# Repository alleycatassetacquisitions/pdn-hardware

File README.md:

# pdn-hardware
The PCB's for Alleycat's Portable Data Node

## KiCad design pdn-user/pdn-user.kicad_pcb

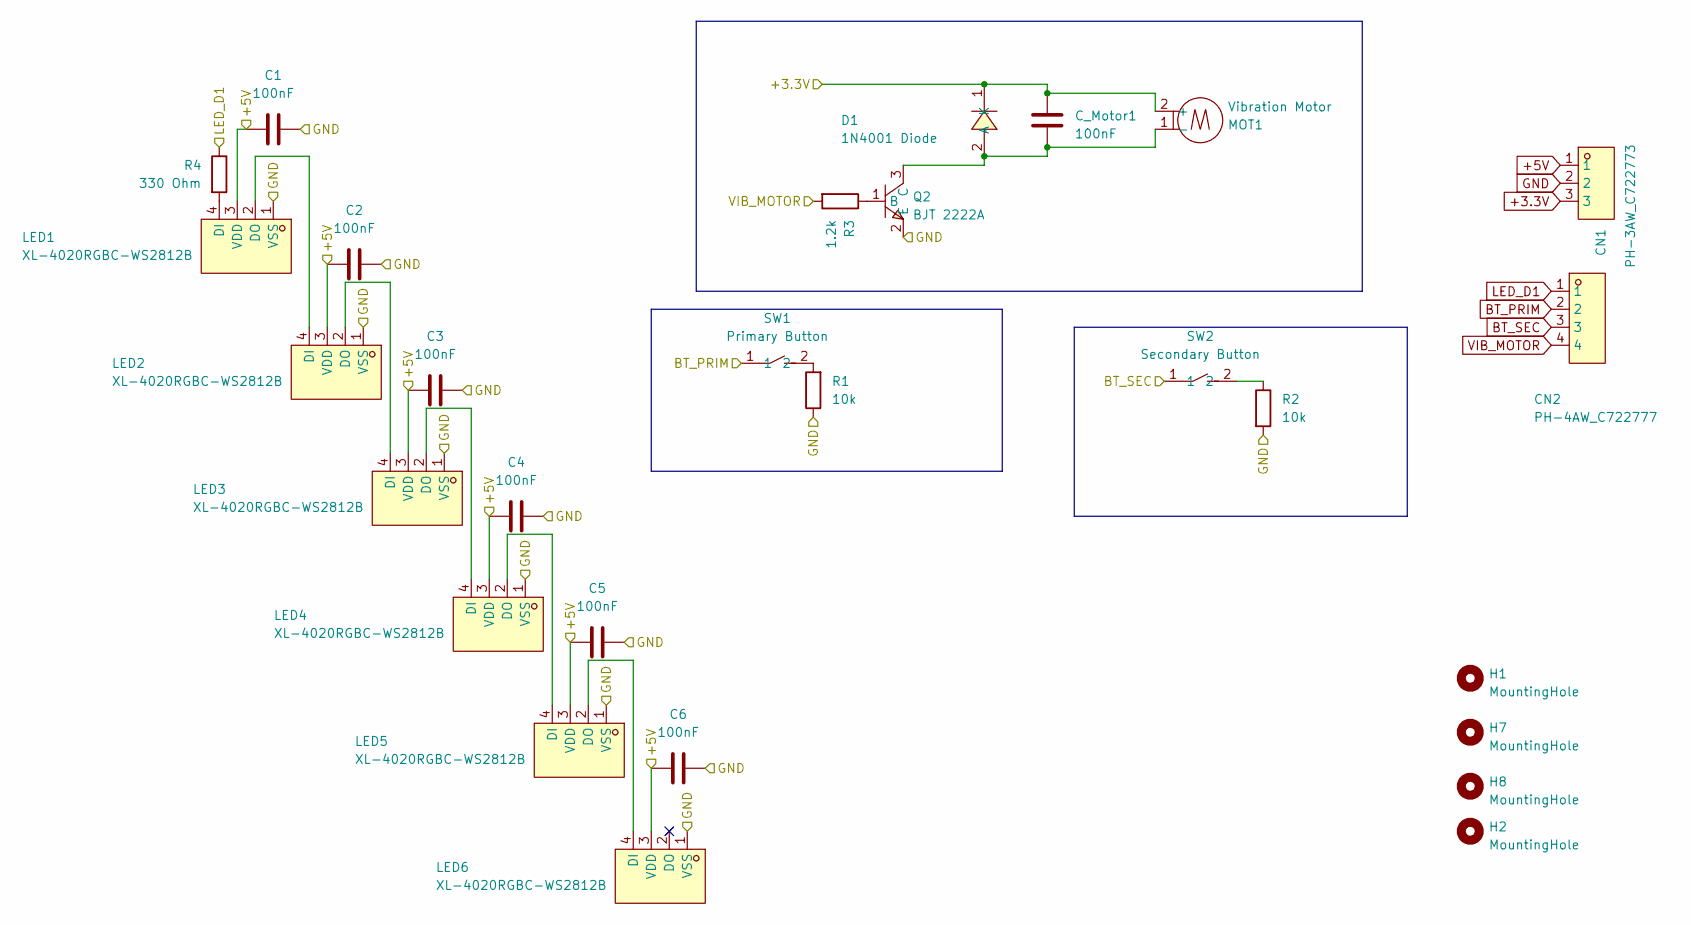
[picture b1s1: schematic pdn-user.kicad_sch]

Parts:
C1, C2, C3, C4, C5, C6: 100nF; C0402; LCSC Part C387958
CN1: PH-3AW_C722773; CONN-TH_PH-3AW; LCSC Part C722773
CN2: PH-4AW_C722777; CONN-TH_PH-4AW_C722777; LCSC Part C722777
C_Motor1: 100nF; C0402; LCSC Part C387958
D1: 1N4001 Diode; SMA_L4.2-W2.6-LS5.0-RD; LCSC Part C2909965
H1, H2, H7, H8: MountingHole; MountingHole_2.2mm_M2_Pad_TopBottom
LED1, LED2, LED3, LED4, LED5, LED6: XL-4020RGBC-WS2812B; LED-SMD_4P-L4.0-W1.7_XL-4020RGBC-WS2812B; LCSC Part C3647024
MOT1: Vibration Motor; VIBRATING-MOTOR-SMD_WELDING; LCSC Part C2759984
Q2: BJT 2222A; SOT-23-3_L2.9-W1.3-P1.90-LS2.4-BR; LCSC Part C916372
R1, R2: 10k; R_0603_1608Metric; LCSC Part C103199
R3: 1.2k; R_0402_1005Metric; LCSC Part C3017481
R4: 330 Ohm; R_0603_1608Metric; LCSC Part C23138
SW1: Primary Button; KEY-SMD_L6.0-W3.5-LS8.0; LCSC Part C2888463
SW2: Secondary Button; KEY-SMD_L6.0-W3.5-LS8.0; LCSC Part C2888463

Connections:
+3.3V: CN1.3, C_Motor1.2, D1.1 (K), MOT1.2 (+)
+5V: C1.1, C2.1, C3.1, C4.1, C5.1, C6.1, CN1.1, LED1.3 (VDD), LED2.3 (VDD), LED3.3 (VDD), LED4.3 (VDD), LED5.3 (VDD), LED6.3 (VDD)
BT_PRIM: CN2.2, SW1.1
BT_SEC: CN2.3, SW2.1
GND: C1.2, C2.2, C3.2, C4.2, C5.2, C6.2, CN1.2, LED1.1 (VSS), LED2.1 (VSS), LED3.1 (VSS), LED4.1 (VSS), LED5.1 (VSS), LED6.1 (VSS), Q2.2 (E), R1.1, R2.2
LED_D1: CN2.1, R4.1
unnamed: C_Motor1.1, D1.2 (A), MOT1.1 (-), Q2.3 (C)
unnamed: LED1.4 (DI), R4.2
unnamed: LED1.2 (DO), LED2.4 (DI)
unnamed: LED2.2 (DO), LED3.4 (DI)
unnamed: LED3.2 (DO), LED4.4 (DI)
unnamed: LED4.2 (DO), LED5.4 (DI)
unnamed: LED5.2 (DO), LED6.4 (DI)
unnamed: Q2.1 (B), R3.1
unnamed: R1.2, SW1.2
unnamed: R2.1, SW2.2
VIB_MOTOR: CN2.4, R3.2

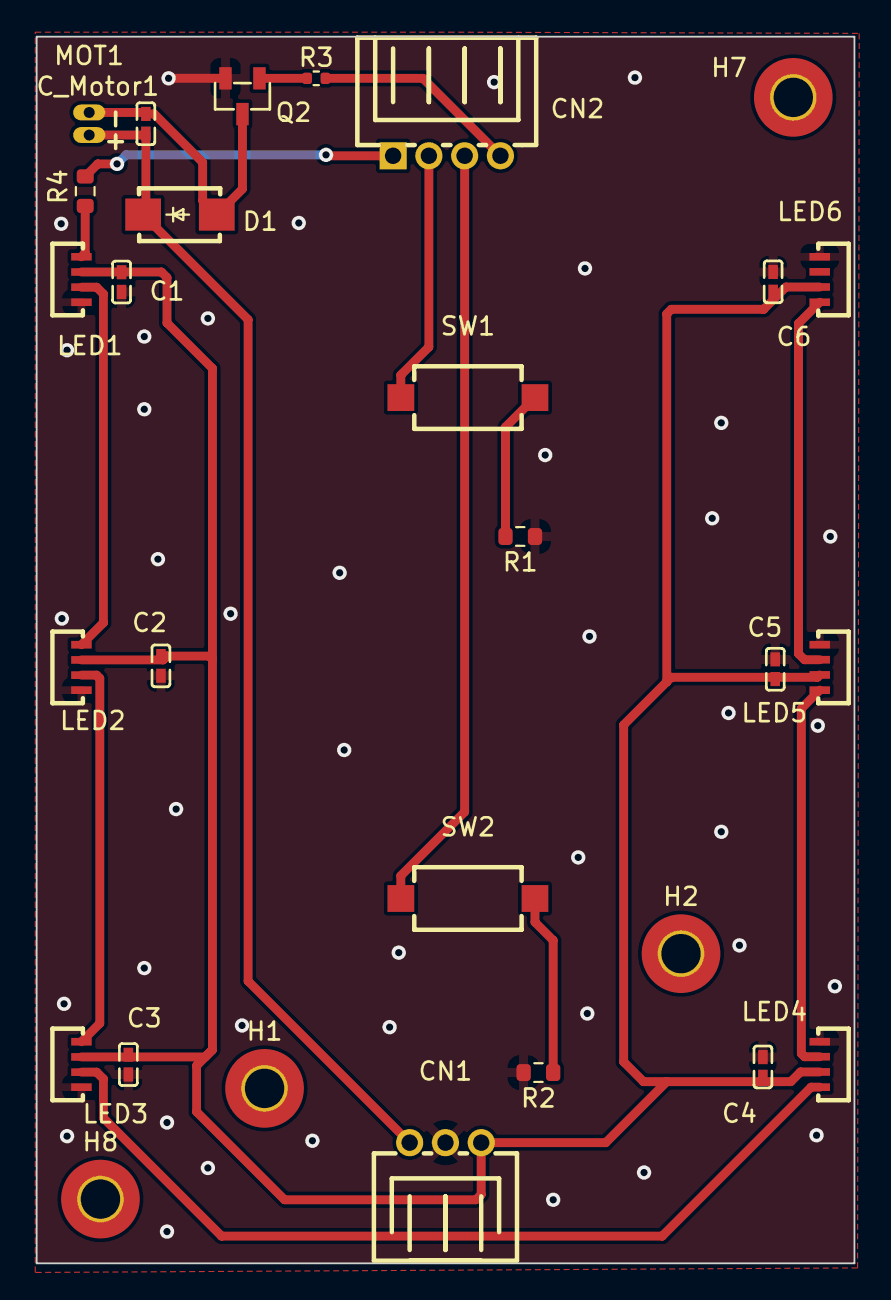
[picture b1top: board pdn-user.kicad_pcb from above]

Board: 2 copper layers, 45.7 x 68.6 mm, 28 parts (0 on the bottom side), 17 nets.

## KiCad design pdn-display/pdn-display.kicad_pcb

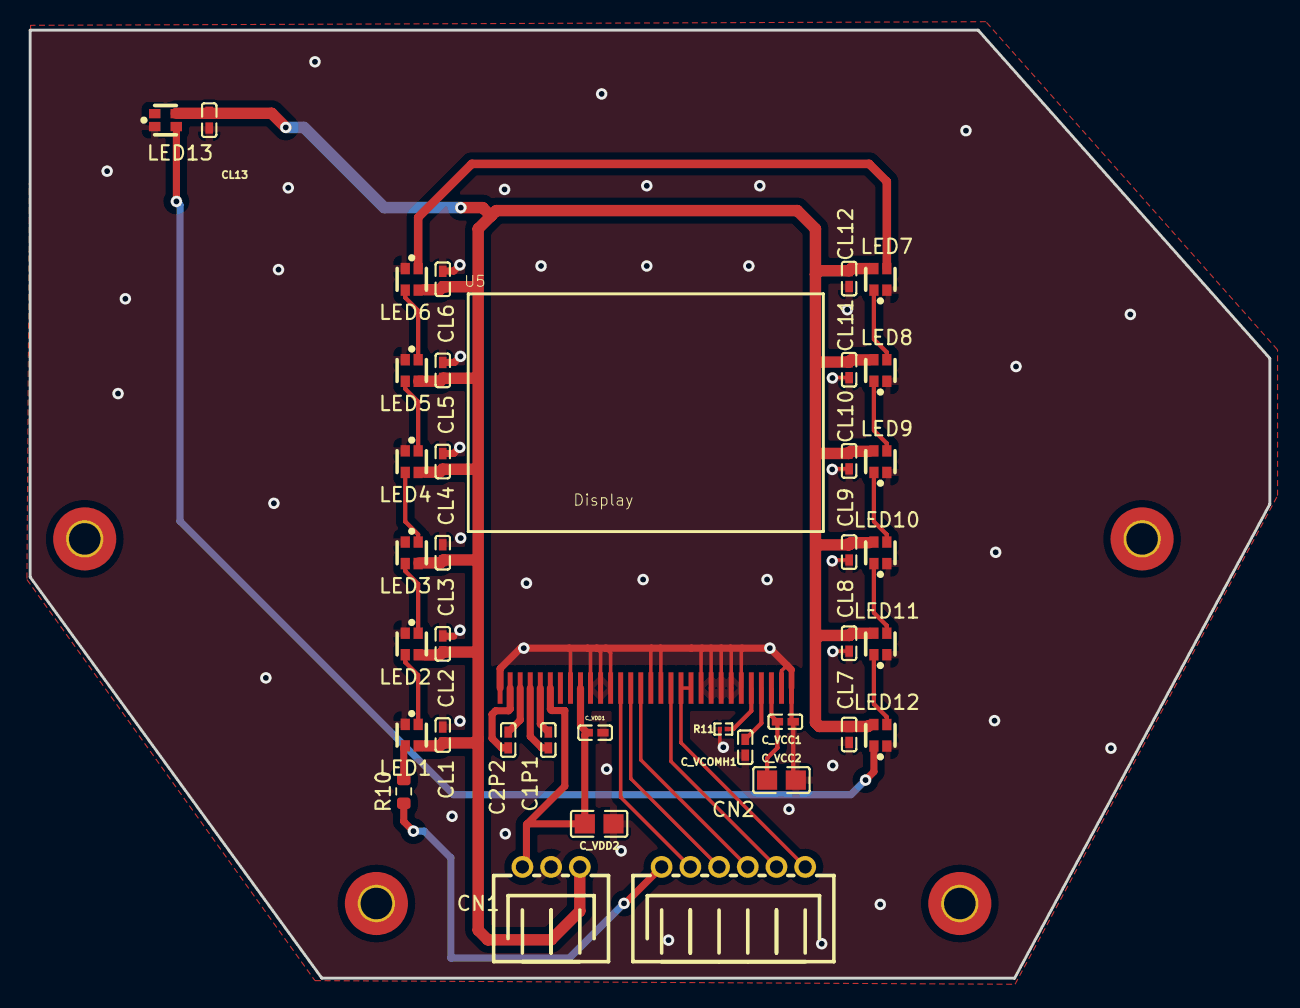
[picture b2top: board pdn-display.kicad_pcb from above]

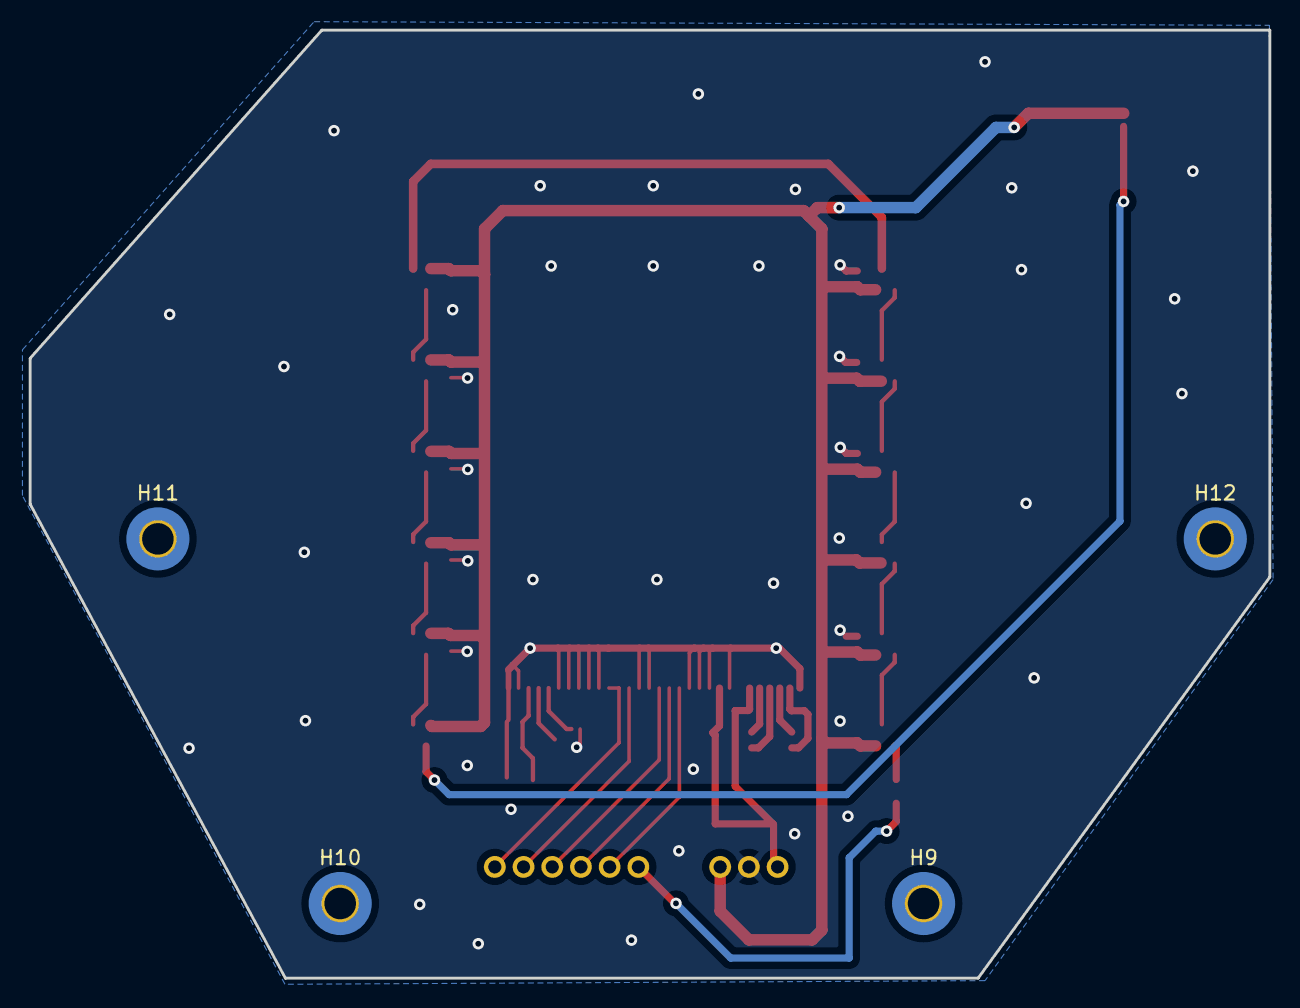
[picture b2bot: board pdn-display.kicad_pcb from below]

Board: 2 copper layers, 86.4 x 66.0 mm, 42 parts (4 on the bottom side), 29 nets.

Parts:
C1P1, C2P2: 1uF; C0402
CL1, CL2, CL3, CL4, CL5, CL6, CL7, CL8, CL9, CL10, CL11, CL12, CL13: 100nF; C0402
CN1: PH-3AW_C722773; CONN-TH_PH-3AW
CN2: PH-6AW_C722785; CONN-TH_PH-6AW
C_VCC1: 100nF; C0402
C_VCC2: 4.7uF; C0805
C_VCOMH1: 2.2uF; C0402
C_VDD1: 100nF; C0402
C_VDD2: 4.7uF; C0805
H9, H10, H11, H12: MountingHole; MountingHole_2.2mm_M2_Pad_TopBottom
LED1, LED2, LED3, LED4, LED5, LED6, LED7, LED8, LED9, LED10, LED11, LED12, LED13: WS2812B; LED-SMD_4P-L1.6-W1.5_XL-1615RGBC-WS2812B
R10: 330 Ohm; R_0603_1608Metric
R11: 1.8M; R0201
U5: Display; SSD1315 FLAT

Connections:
/+3.3V: C_VDD1.2, C_VDD2.2, U5.6 (VBAT), U5.9 (VDD)
/+5V: CL1.1, CL2.1, CL3.1, CL4.1, CL5.1, CL6.1, CL7.1, CL8.1, CL9.1, CL10.1, CL11.1, CL12.1, CL13.1, CN1.1, LED1.2 (VDD), LED2.2 (VDD), LED3.2 (VDD), LED4.2 (VDD), LED5.2 (VDD), LED6.2 (VDD), LED7.2 (VDD), LED8.2 (VDD), LED9.2 (VDD), LED10.2 (VDD), LED11.2 (VDD), LED12.2 (VDD), LED13.2 (VDD)
/CS: CN2.5, U5.13 (/CS)
/DC: CN2.3, U5.15 (DC/I2C_SA0)
/GND: CL1.2, CL2.2, CL3.2, CL4.2, CL5.2, CL6.2, CL7.2, CL8.2, CL9.2, CL10.2, CL11.2, CL12.2, CL13.2, CN1.2, C_VCC1.1, C_VCC2.1, C_VCOMH1.2, C_VDD1.1, C_VDD2.1, LED1.3 (GND), LED2.3 (GND), LED3.3 (GND), LED4.3 (GND), LED5.3 (GND), LED6.3 (GND), LED7.3 (GND), LED8.3 (GND), LED9.3 (GND), LED10.3 (GND), LED11.3 (GND), LED12.3 (GND), LED13.3 (GND), R11.1, U5.1 (NC(GND)@1), U5.8 (VSS), U5.10 (BS0), U5.11 (BS1), U5.12 (BS2), U5.16 (R/W), U5.17 (E/RD), U5.21 (D3), U5.22 (D4), U5.23 (D5), U5.24 (D6), U5.25 (D7), U5.29 (VLSS), U5.30 (NC(GND)@2)
/LED_D2: CN2.6, R10.1
/RESET: CN2.4, U5.14 (/RES)
/SCLK: CN2.2, U5.18 (D0/SPI_SCLK/I2C_SCK)
/SDIN: CN2.1, U5.19 (D1/SPI_SDIN/I2C_SDA), U5.20 (D2/I2C_SDA)
unnamed: LED1.4 (DI), R10.2
unnamed: LED1.1 (DO), LED2.4 (DI)
unnamed: LED2.1 (DO), LED3.4 (DI)
unnamed: LED3.1 (DO), LED4.4 (DI)
unnamed: LED4.1 (DO), LED5.4 (DI)
unnamed: LED5.1 (DO), LED6.4 (DI)
unnamed: LED6.1 (DO), LED7.4 (DI)
unnamed: LED7.1 (DO), LED8.4 (DI)
unnamed: LED8.1 (DO), LED9.4 (DI)
unnamed: LED9.1 (DO), LED10.4 (DI)
unnamed: LED10.1 (DO), LED11.4 (DI)
unnamed: LED11.1 (DO), LED12.4 (DI)
unnamed: LED12.1 (DO), LED13.4 (DI)
unnamed: C1P1.1, U5.5 (C1N)
unnamed: C1P1.2, U5.4 (C1P)
unnamed: C2P2.1, U5.3 (C2N)
unnamed: C2P2.2, U5.2 (C2P)
unnamed: R11.2, U5.26 (IREF)
unnamed: C_VCC1.2, C_VCC2.2, U5.28 (VCC)
unnamed: C_VCOMH1.1, U5.27 (VCOMH)

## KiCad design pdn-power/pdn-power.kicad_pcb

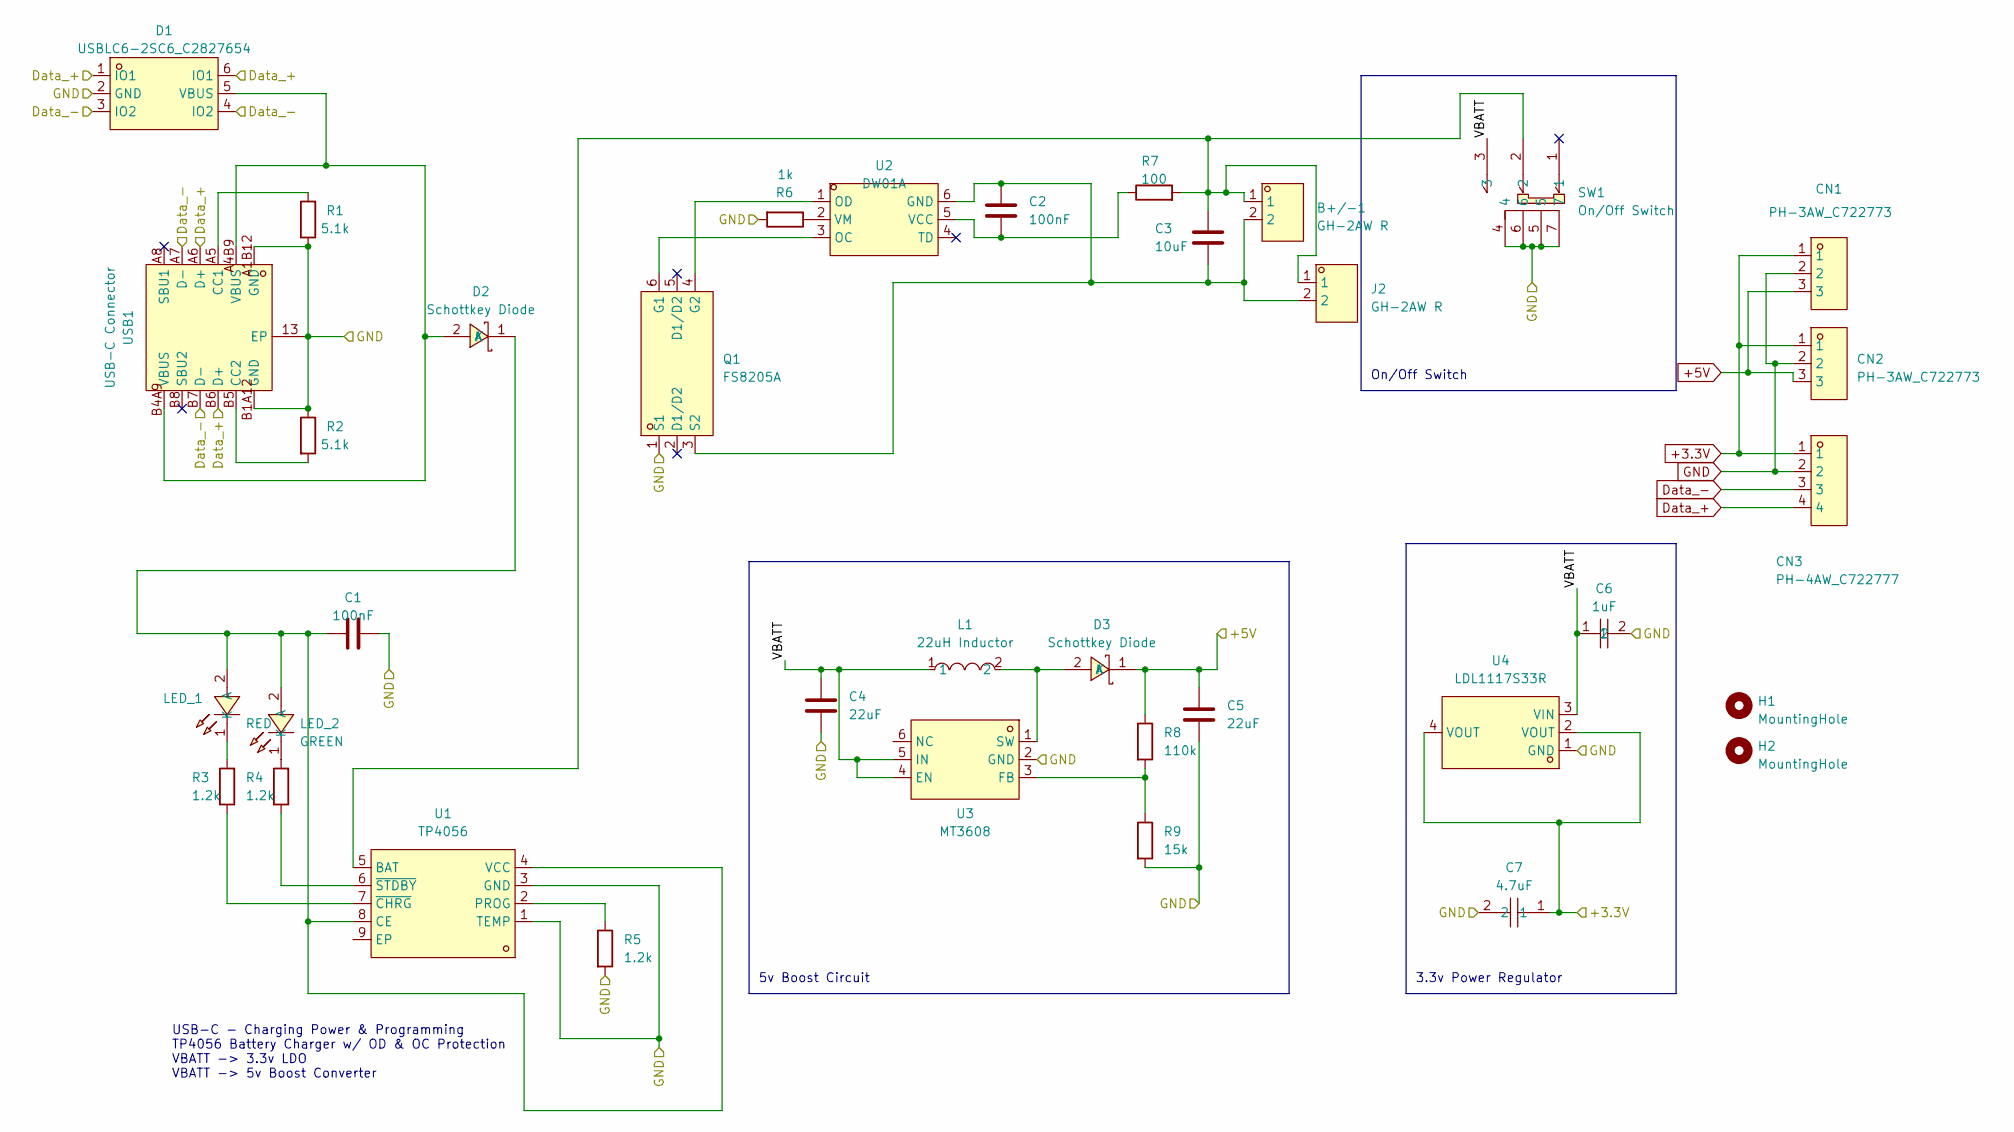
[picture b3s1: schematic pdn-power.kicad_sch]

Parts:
B+/-1: GH-2AW R; CONN-TH_GH 1x2P 1.25mm; LCSC Part C7433528
C1, C2: 100nF; C0402; LCSC Part C387958
C3: 10uF; C0805; LCSC Part C1222438
C4, C5: 22uF; C_1206_3216Metric; LCSC Part C12891
C6: 1uF; C0402; LCSC Part C29266
C7: 4.7uF; C0805; LCSC Part C274245
CN1, CN2: PH-3AW_C722773; CONN-TH_PH-3AW; LCSC Part C722773
CN3: PH-4AW_C722777; CONN-TH_PH-4AW_C722777; LCSC Part C722777
D1: USBLC6-2SC6_C2827654; SOT-23-6_L2.9-W1.6-P0.95-LS2.8-BL; LCSC Part C2827654
D2, D3: Schottkey Diode; SMA_L4.3-W2.6-LS5.2-RD; LCSC Part C8678
H1, H2: MountingHole; MountingHole_2.2mm_M2_Pad_TopBottom
J2: GH-2AW R; CONN-TH_GH 1x2P 1.25mm; LCSC Part C7433528
L1: 22uH Inductor; IND-SMD_L7.0-W6.8; LCSC Part C27442
LED_1: RED; LED0603-RD_RED; LCSC Part C965799
LED_2: GREEN; LED0603-RD_RED; LCSC Part C965804
Q1: FS8205A; SOT-23-6_L2.9-W1.6-P0.95-LS2.8-BR; LCSC Part C908265
R1, R2: 5.1k; R_0402_1005Metric; LCSC Part C25905
R3, R4, R5: 1.2k; R_0402_1005Metric; LCSC Part C3017481
R6: 1k; R_0603_1608Metric; LCSC Part C2759381
R7: 100; R_0402_1005Metric; LCSC Part C327795
R8: 110k; R_0805_2012Metric; LCSC Part CR0805J80114G
R9: 15k; R_0402_1005Metric; LCSC Part C474072
SW1: On/Off Switch; SW-SMD_SS-1290; LCSC Part C589295
U1: TP4056; ESOP-8_L4.9-W3.9-P1.27-LS6.0-BL-EP; LCSC Part C382139
U2: DW01A; SOT-23-6_L2.9-W1.6-P0.95-LS2.8-BL; LCSC Part C351410
U3: MT3608; SOT-23-6_L2.9-W1.6-P0.95-LS2.8-BL; LCSC Part C84817
U4: LDL1117S33R; SOT-223-4_L6.5-W3.5-P2.30-LS7.0-BR; LCSC Part C435835
USB1: USB-C Connector; USB-C-SMD_TYPE-C-16P-1; LCSC Part C2982555

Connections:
+3.3V: C7.1, CN1.1, CN2.1, CN3.1, U4.2 (VOUT), U4.4 (VOUT)
+5V: C5.2, CN1.3, CN2.3, D3.1 (K), R8.1
/VBATT: C4.2, C6.1, L1.1, SW1.3, U3.4 (EN), U3.5 (IN), U4.3 (VIN)
Data_+: CN3.4, D1.1 (IO1), D1.6 (IO1), USB1.A6 (D+), USB1.B6 (D+)
Data_-: CN3.3, D1.3 (IO2), D1.4 (IO2), USB1.A7 (D-), USB1.B7 (D-)
GND: C1.2, C4.1, C5.1, C6.2, C7.2, CN1.2, CN2.2, CN3.2, D1.2 (GND), Q1.1 (S1), R1.1, R2.1, R5.2, R6.2, R9.2, SW1.4, SW1.5, SW1.6, SW1.7, U1.1 (TEMP), U1.3 (GND), U3.2 (GND), U4.1 (GND), USB1.13 (EP), USB1.A1B12 (GND), USB1.B1A12 (GND)
unnamed: D1.5 (VBUS), D2.2 (A), USB1.A4B9 (VBUS), USB1.B4A9 (VBUS)
unnamed: C1.1, D2.1 (K), LED_1.2 (A), LED_2.2 (A), U1.4 (VCC), U1.8 (CE)
unnamed: D3.2 (A), L1.2, U3.1 (SW)
unnamed: LED_1.1 (K), R3.2
unnamed: LED_2.1 (K), R4.2
unnamed: Q1.6 (G1), U2.3 (OC)
unnamed: Q1.4 (G2), U2.1 (OD)
unnamed: B+/-1.2, C2.1, C3.2, J2.2, Q1.3 (S2), U2.6 (GND)
unnamed: B+/-1.1, C3.1, J2.1, R7.2, SW1.2, U1.5 (BAT)
unnamed: R5.1, U1.2 (PROG)
unnamed: R3.1, U1.7 (~CHRG)
unnamed: R4.1, U1.6 (~STDBY)
unnamed: C2.2, R7.1, U2.5 (VCC)
unnamed: R6.1, U2.2 (VM)
unnamed: R8.2, R9.1, U3.3 (FB)
unnamed: R1.2, USB1.A5 (CC1)
unnamed: R2.2, USB1.B5 (CC2)

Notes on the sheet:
On/Off Switch
3.3v Power Regulator
5v Boost Circuit
USB-C - Charging Power & Programming TP4056 Battery Charger w/ OD & OC Protection VBATT -> 3.3v LDO VBATT -> 5v Boost Converter

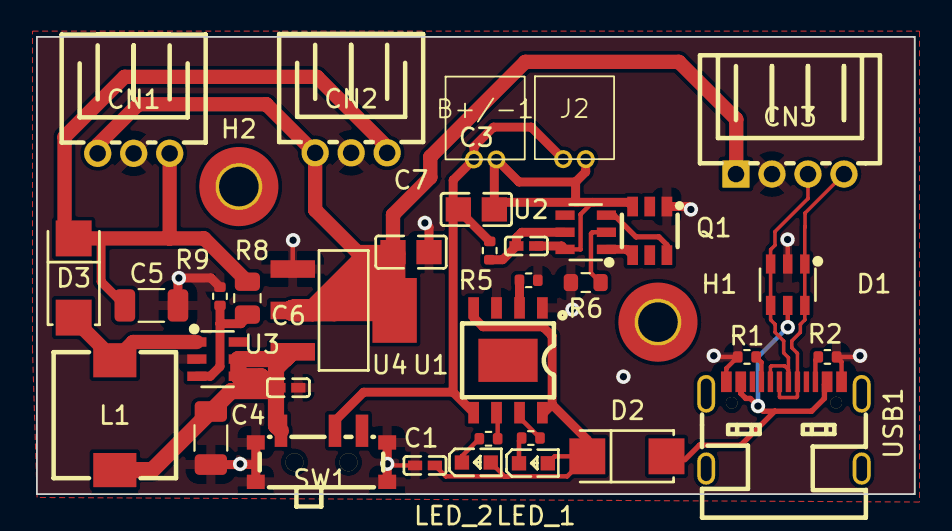
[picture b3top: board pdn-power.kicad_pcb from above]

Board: 2 copper layers, 48.8 x 25.4 mm, 36 parts (0 on the bottom side), 23 nets.

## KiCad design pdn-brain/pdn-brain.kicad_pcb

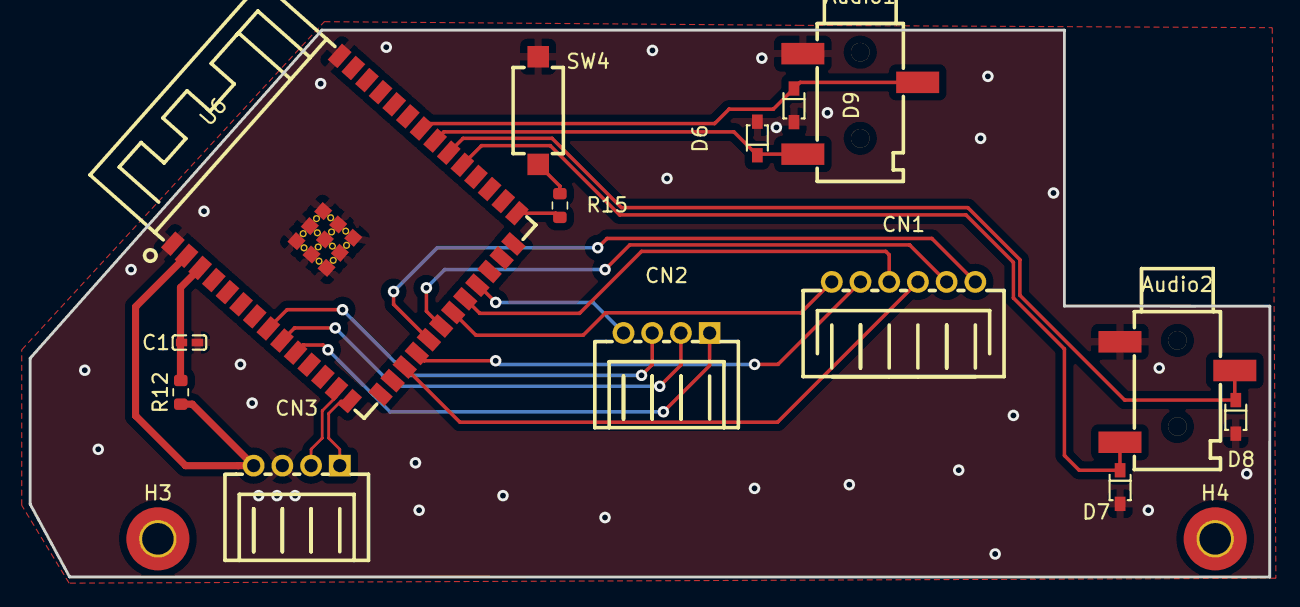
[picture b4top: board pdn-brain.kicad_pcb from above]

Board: 2 copper layers, 86.4 x 38.1 mm, 16 parts (0 on the bottom side), 21 nets.

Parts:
Audio1: TX Jack; AUDIO-SMD_PJ-320B
Audio2: RX Jack; AUDIO-SMD_PJ-320B
C1: 1uF; C0402
CN1: PH-6AW_C722785; CONN-TH_PH-6AW
CN2, CN3: PH-4AW_C722777; CONN-TH_PH-4AW_C722777
D6, D7, D8, D9: TVS Diode; SOD-323_L1.8-W1.3-LS2.5-RD
H3, H4: MountingHole; MountingHole_2.2mm_M2_Pad_TopBottom
R12: 10k; R_0603_1608Metric
R15: 1k; R_0603_1608Metric
SW4: BOOT; KEY-SMD_L6.0-W3.5-LS8.0
U6: ESP32-S3-WROOM-1(N8R8); WIRELM-SMD_ESP32-S3-WROOM-1

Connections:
/+3.3V: R12.1, U6.2 (3V3)
/BT_PRIM: CN2.3, U6.8 (IO15)
/BT_SEC: CN2.2, U6.9 (IO16)
/CS: CN1.5, U6.18 (IO10)
/DC: CN1.3, U6.17 (IO9)
/Data_+: CN3.1, U6.14 (IO20)
/Data_-: CN3.2, U6.13 (IO19)
/GND: Audio1.1, Audio2.1, C1.1, CN3.3, D6.2 (A), D7.2 (A), D8.2 (A), D9.2 (A), SW4.2, U6.1 (GND), U6.40 (GND), U6.41 (GND)
/LED_D1: CN2.4, U6.23 (IO21)
/LED_D2: CN1.6, U6.21 (IO13)
/RESET: CN1.4, U6.22 (IO14)
/SCLK: CN1.2, U6.20 (IO12)
/SDIN: CN1.1, U6.19 (IO11)
/VIB_MOTOR: CN2.1, U6.10 (IO17)
unnamed: Audio1.2 (D+), D9.1 (C), U6.34 (IO41)
unnamed: Audio1.3 (D-), D6.1 (C), U6.33 (IO40)
unnamed: Audio2.3 (D+), D7.1 (C), U6.31 (IO38)
unnamed: Audio2.2 (D-), D8.1 (C), U6.32 (IO39)
unnamed: R15.1, SW4.1
unnamed: C1.2, R12.2, U6.3 (EN)
unnamed: R15.2, U6.27 (IO0)

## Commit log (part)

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2024-05-03 Initial commit.
2024-07-17 Broke out PCB's into separate projects.
2024-12-02 2025 Production Files.
